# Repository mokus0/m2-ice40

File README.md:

This is a work in progress.  The end goal is to develop a m.2 3042 B-key (USB) board to install into my System76 Galago Pro laptop's internal 3G/LTE module socket, to provide a debugging and development tool for work on the system's Embedded Controller.

In particular, this board will include:
* a Lattice Semiconductor ICE40 FPGA with programming and USB interface (based on FTDI FT2232H high-speed USB interface as used in the "iCEstick" dev board, but upgraded from HX1K to HX4K FPGA)
* a MAX6621 I2C-to-PECI translator, to experiment with
* configurable power source; run from either 3.3v provided to the m.2 module or a wire to steal power from somewhere else in the system
* pads to connect FPGA as desired to various nets on the system board for monitoring and logging
* TODO (maybe in a second rev, and space permitting): a small microcontroller, perhaps STM32L4R5

Intended uses include:
* Investigating the traffic on the LPC bus, to develop sufficient understanding to be able to implement the bus in a new non-ITE processor, and later to monitor that processor's usage of the LPC bus for correctness
* Ability to log and monitor behavior of EC long-term

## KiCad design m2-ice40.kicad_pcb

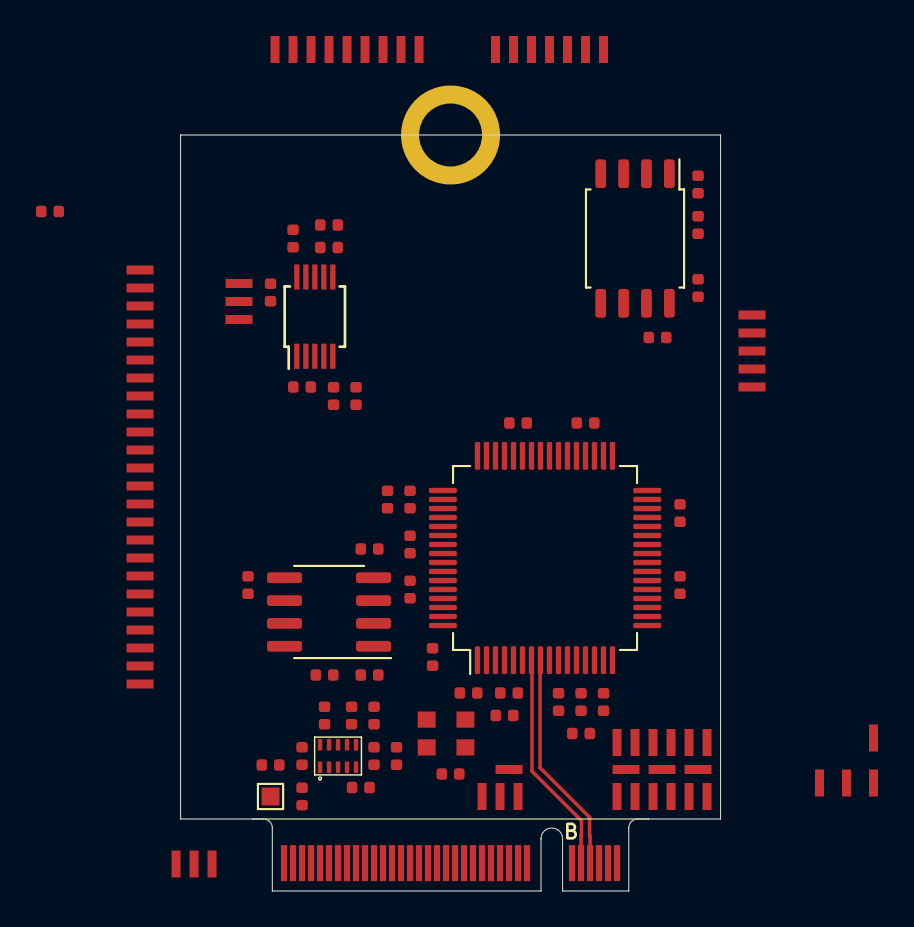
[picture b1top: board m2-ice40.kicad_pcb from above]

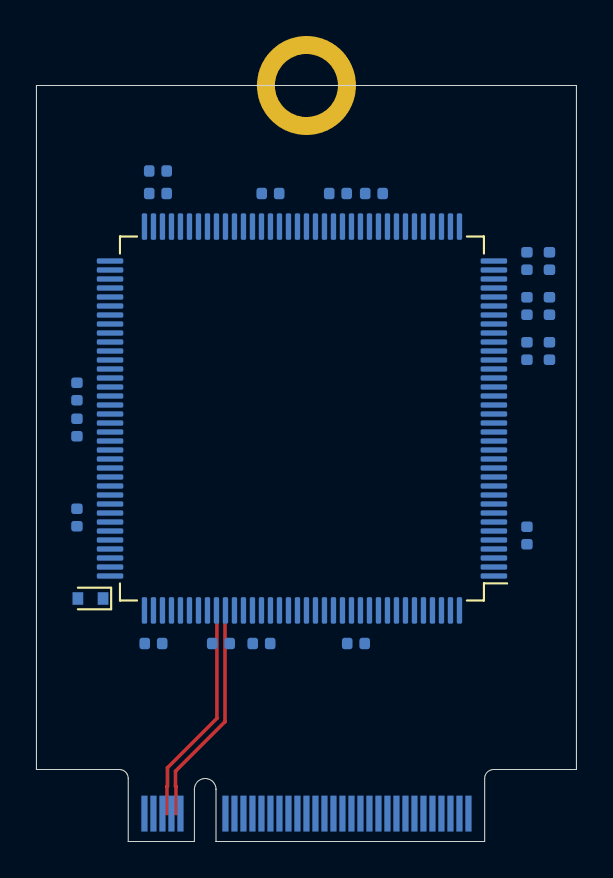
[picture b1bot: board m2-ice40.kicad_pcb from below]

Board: 4 copper layers, 30.0 x 42.0 mm, 146 parts (21 on the bottom side), 123 nets.

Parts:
C201, C202, C204, C207, C208, C209, C210, C211, C212, C213, C214, C215, C301, C302, C303, C304, C305, C306, C307, C308, C401, C402, C403, C406, C407, C408, C409, C701, C702: 0.1u; C_0402_1005Metric
C203, C404, C410, C503, C504: 10u; C_0402_1005Metric
C205, C206, C501: 4.7u; C_0402_1005Metric
C405: 0.01u; C_0402_1005Metric
C502: 120p; C_0402_1005Metric
D401: CDBU0520; D_SOD-523
J601: m.2_socket2_module; m2-padKeyB
J602: M.2-GND-MOUNTING; m.2_mechanical_ground_pad
R201, R203, R206, R401, R402, R403, R404, R701: 10k; R_0402_1005Metric
R202, R501, R502, R702: 0; R_0402_1005Metric
R204, R703, R704, R705: 2.2k; R_0402_1005Metric
R205: 12k 1%; R_0402_1005Metric
R207: 12k; R_0402_1005Metric
R405: 100; R_0402_1005Metric
R503, R504, R505: 100k; R_0402_1005Metric
TP101: PECI_VREF; TestPoint_Pad_0.5x1.5mm
TP102: PECI; TestPoint_Pad_0.5x1.5mm
TP103: PECI_GND; TestPoint_Pad_0.5x1.5mm
TP501: 3.3V_EXT; TestPoint_Pad_1.0x1.0mm
TP701, TP702, TP703, TP704, TP705, TP706, TP707, TP708, TP709, TP710, TP711, TP712, TP713, TP714, TP715, TP716, TP717, TP718, TP719, TP720, TP721, TP722, TP723, TP724, TP725, TP726, TP727, TP728, TP729, TP730, TP731, TP732, TP733, TP734, TP735, TP736, TP737, TP738, TP739, TP740, TP741, TP742, TP743, TP744, TP745, TP746, TP747, TP748, TP749, TP750, TP751, TP752, TP753, TP754, TP755, TP756, TP757, TP758, TP759, TP760, TP761, TP762, TP763, TP764, TP765, TP766, TP767, TP768, TP769, TP770, TP771: TestPoint; TestPoint_Pad_0.5x1.5mm
U201: 93LC56C-I/SN; SOIC-8_3.9x4.9mm_P1.27mm
U202: FT2232H; LQFP-64_10x10mm_P0.5mm
U301: ICE40HX1K-TQ144; TQFP-144_20x20mm_P0.5mm
U401: W25Q80DVSNIG; SOIC-8_5.23x5.23mm_P1.27mm
U501: TPSM82821; SIL0010D
U701: MAX6621; MSOP-10_3x3mm_P0.5mm
X201: DSC6001JI2A-012.0000; Oscillator_SMD_EuroQuartz_XO32-4Pin_3.2x2.5mm

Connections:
/FPGA/1.8v_OD_SIM_DETECT: J601.66, U301.139
/FPGA/ACBUS0: U202.26, U301.97
/FPGA/ACBUS1: U202.27, U301.96
/FPGA/ACBUS2: U202.28, U301.95
/FPGA/ACBUS3: U202.29, U301.91
/FPGA/ACBUS4: U202.30, U301.90
/FPGA/ACBUS5: U202.32, U301.88
/FPGA/ACBUS6: U202.33, U301.87
/FPGA/ACBUS7: U202.34, U301.81
/FPGA/ADBUS7: U202.24, U301.98
/FPGA/DISABLE#: J601.8, U301.121
/FPGA/FTDI_CTS: U202.19, U301.104
/FPGA/FTDI_DCD: U202.23, U301.99
/FPGA/FTDI_DSR: U202.22, U301.101
/FPGA/FTDI_DTR: U202.21, U301.102
/FPGA/FTDI_RTS: U202.18, U301.105
/FPGA/FTDI_RX__ICE_TX: U202.17, U301.106
/FPGA/FTDI_TX__ICE_RX: U202.16, U301.107
/FPGA/ICE_CLK: R202.1, U301.129
/FPGA/PECI_RESET#: R701.1, U301.39, U701.8
/FPGA/PECI_SCL: R705.2, U301.42, U701.5
/FPGA/PECI_SDA: R704.2, U301.41, U701.4
/FPGA/POWER_OFF#: J601.6, U301.120
/FPGA/RESET#: J601.67, U301.141
/FPGA/UIM_CLK: J601.32, U301.136
/FPGA/UIM_DATA: J601.34, U301.137
/FPGA/UIM_PWR: J601.36, U301.138
/FPGA/UIM_RESET: J601.30, U301.135
/fpga power and config/1.2V: C405.1, C406.1, C407.1, C408.1, C409.1, C410.1, C502.1, C503.1, C504.1, R405.1, R503.1, R504.1, U301.27, U301.51, U301.92, U301.111, U501.5, U501.6, U501.7
/fpga power and config/3.3V: C201.1, C202.1, C205.1, C206.1, C207.1, C208.1, C209.1, C211.1, C213.1, C215.1, C301.1, C302.1, C303.1, C304.1, C305.1, C306.1, C307.1, C308.1, C401.1, C402.1, C501.1, C701.1, D401.2, R201.1, R203.1, R206.1, R207.1, R401.1, R402.2, R403.2, R404.1, R501.1, R502.1, R701.2, R703.1, R704.1, R705.1, U201.6, U201.8, U202.4, U202.9, U202.20, U202.31, U202.42, U202.50, U202.56, U301.6, U301.30, U301.46, U301.57, U301.72, U301.89, U301.100, U301.123, U301.133, U401.8, U501.1, U501.2, U501.3, U701.6, X201.1, X201.4
/fpga power and config/CDONE: U202.45, U301.65
/fpga power and config/CRESET: R404.2, U202.46, U301.66
/fpga power and config/GNDPLL: C403.2, C404.2, U301.35
/fpga power and config/VCCPLL: C403.1, C404.1, R405.2, U301.36
/ftdi/FTDI_1.8V: C203.1, C204.1, C210.1, C212.1, C214.1, U202.12, U202.37, U202.49, U202.64
/ftdi/ICE_MISO: U202.40, U301.68, U401.2
/ftdi/ICE_MOSI: U202.39, U301.67, U401.5
/ftdi/ICE_SCK: U202.38, U301.70, U401.6
/ftdi/ICE_SS_B: R401.2, U202.43, U301.71, U401.1
/ftdi/USB_D+: J601.7, U202.8
/ftdi/USB_D-: J601.9, U202.7
/m2-conn/3.3V: J601.2, J601.4, J601.70, J601.72, J601.74, R501.2
/peci/ALERT#: R703.2, U301.38, U701.9
/peci/PECI: TP102.1, U701.1
/peci/PECI_GND: C702.2, R702.1, TP103.1, U701.2
/peci/PECI_VREF: C702.1, TP101.1, U701.10
GND: C201.2, C202.2, C203.2, C204.2, C205.2, C206.2, C207.2, C208.2, C209.2, C210.2, C211.2, C212.2, C213.2, C214.2, C215.2, C301.2, C302.2, C303.2, C304.2, C305.2, C306.2, C307.2, C308.2, C401.2, C402.2, C405.2, C406.2, C407.2, C408.2, C409.2, C410.2, C501.2, C503.2, C504.2, C701.2, J601.3, J601.5, J601.11, J601.21, J601.27, J601.33, J601.39, J601.45, J601.51, J601.57, J601.71, J601.73, J602.1, R205.1, R505.2, R702.2, TP764.1, TP765.1, TP766.1, TP767.1, TP768.1, TP769.1, TP770.1, TP771.1, U201.5, U202.1, U202.5, U202.10, U202.11, U202.13, U202.15, U202.25, U202.35, U202.47, U202.51, U301.5, U301.13, U301.14, U301.59, U301.69, U301.86, U301.103, U301.132, U301.140, U401.4, U501.9, U501.10, U701.3, U701.7, X201.2
unnamed: C502.2, R504.2, R505.1, U501.8
unnamed: D401.1, U301.108
unnamed: R201.2, R204.2, U201.4
unnamed: R202.2, U202.2, X201.3
unnamed: R203.2, U201.2, U202.62
unnamed: R204.1, U201.3, U202.61
unnamed: R205.2, U202.6
unnamed: R206.2, U201.1, U202.63
unnamed: R207.2, U202.14
unnamed: R402.1, U401.7
unnamed: R403.1, U401.3
unnamed: R502.2, TP501.1
unnamed: R503.2, U501.4
unnamed: TP701.1, U301.112
unnamed: TP702.1, U301.113
unnamed: TP703.1, U301.114
unnamed: TP704.1, U301.115
unnamed: TP705.1, U301.116
unnamed: TP706.1, U301.117
unnamed: TP707.1, U301.118
unnamed: TP708.1, U301.119
unnamed: TP709.1, U301.122
unnamed: TP710.1, U301.128
unnamed: TP711.1, U301.134
unnamed: TP712.1, U301.142
unnamed: TP713.1, U301.143
unnamed: TP714.1, U301.144
unnamed: TP715.1, U301.73
unnamed: TP716.1, U301.74
unnamed: TP717.1, U301.75
unnamed: TP718.1, U301.76
unnamed: TP719.1, U301.78
unnamed: TP720.1, U301.79
unnamed: TP721.1, U301.80
unnamed: TP722.1, U301.93
unnamed: TP723.1, U301.94
unnamed: TP724.1, U301.37
unnamed: TP725.1, U301.43
unnamed: TP726.1, U301.44
unnamed: TP727.1, U301.45
unnamed: TP728.1, U301.47
unnamed: TP729.1, U301.48
unnamed: TP730.1, U301.49
unnamed: TP731.1, U301.50
unnamed: TP732.1, U301.52
unnamed: TP733.1, U301.56
unnamed: TP734.1, U301.58
unnamed: TP735.1, U301.60
unnamed: TP736.1, U301.61
unnamed: TP737.1, U301.62
unnamed: TP738.1, U301.63
unnamed: TP739.1, U301.64
unnamed: TP740.1, U301.1
unnamed: TP741.1, U301.2
unnamed: TP742.1, U301.3
unnamed: TP743.1, U301.4
unnamed: TP744.1, U301.7
unnamed: TP745.1, U301.8
unnamed: TP746.1, U301.9
unnamed: TP747.1, U301.10
unnamed: TP748.1, U301.11
unnamed: TP749.1, U301.12
unnamed: TP750.1, U301.19
unnamed: TP751.1, U301.20
unnamed: TP752.1, U301.21
unnamed: TP753.1, U301.22
unnamed: TP754.1, U301.23
unnamed: TP755.1, U301.24
unnamed: TP756.1, U301.25
unnamed: TP757.1, U301.26
unnamed: TP758.1, U301.28
unnamed: TP759.1, U301.29
unnamed: TP760.1, U301.31
unnamed: TP761.1, U301.32
unnamed: TP762.1, U301.33
unnamed: TP763.1, U301.34

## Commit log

2019-12-15 rough draft of first design
2019-12-15 initial footprint assignment and VERY rough placement
2019-12-16 added a couple more footprints
2019-12-21 local component placement
2019-12-22 assigning pins, adding test points, placing stuff, etc
